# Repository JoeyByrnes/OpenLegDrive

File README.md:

# OpenLeg Drive
Motor Controller for OpenLeg Actuators

This hardware is based on the <a href="https://github.com/mjbots">Moteus r4.5</a> by Josh Pieper at mjbots, and the firmware is ported from Ben Kat's <a href="https://github.com/bgkatz/motorcontrol">motorcontrol</a> project. See the <a href="https://github.com/JoeyByrnes/motorcontrolG4">motorcontrolG4</a> repo for the firmware.

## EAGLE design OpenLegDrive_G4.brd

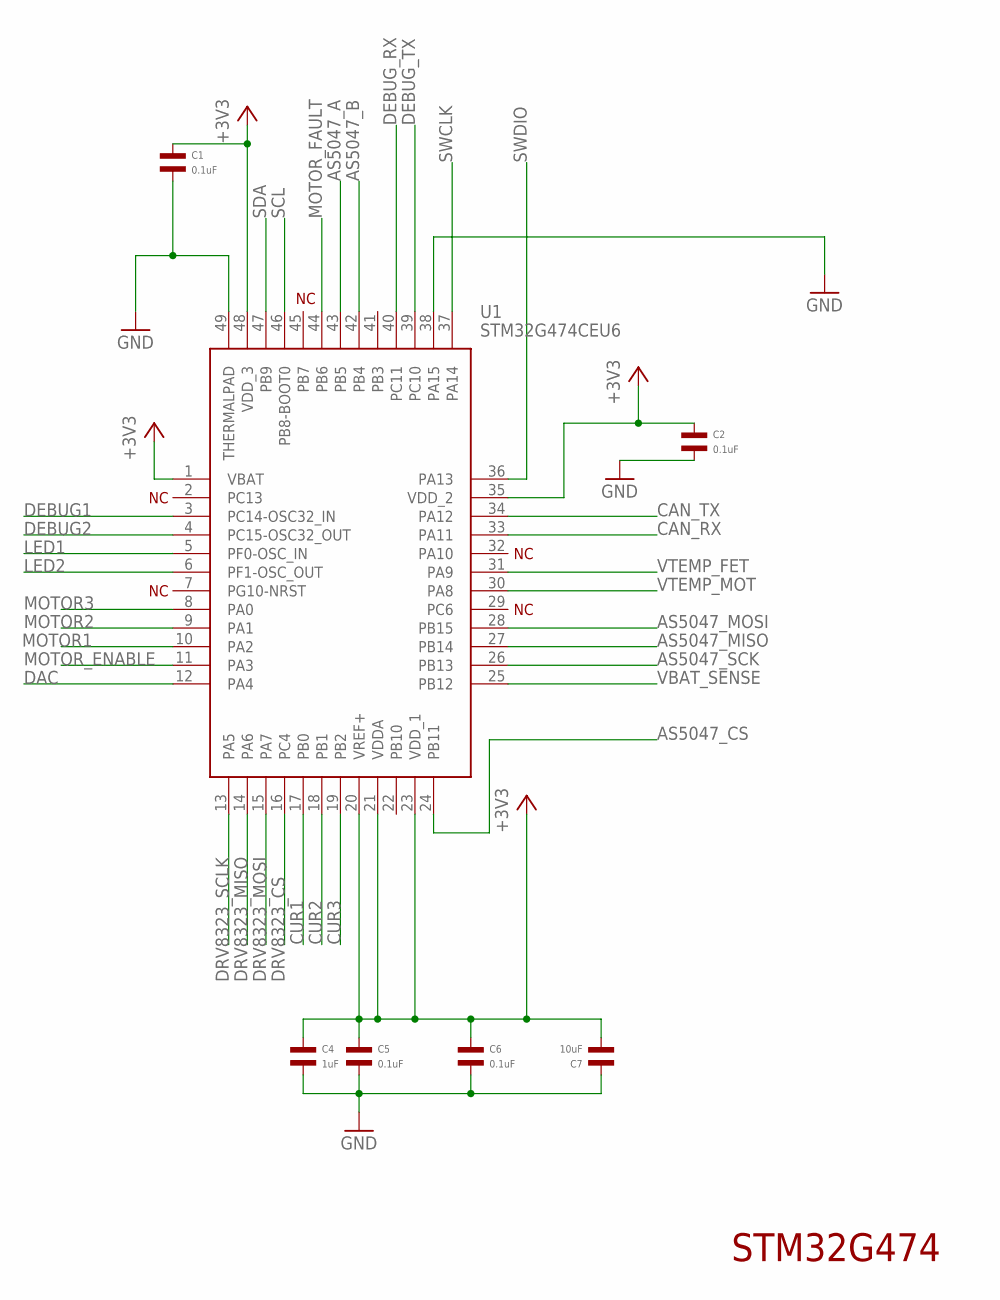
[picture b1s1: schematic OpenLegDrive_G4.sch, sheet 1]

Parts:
C1, C2, C5, C6: 0.1uF; C0402; MPN MF-CAP-0402-0.1uF
C4: 1uF; C0402; MPN MF-CAP-0402-1uF
C7: 10uF; C1206; MPN MF-CAP-1206-10uF
U1: STM32G474CEU6; QFN50P700X700X60-49N; MPN STM32G474CEU6

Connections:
3V3: C1.P$1, C2.P$1, C4.P$1, C5.P$1, C6.P$1, C7.P$2, U1.1 (VBAT), U1.20 (VREF+), U1.21 (VDDA), U1.23 (VDD_1), U1.35 (VDD_2), U1.48 (VDD_3); also elsewhere on the board
AS5047_A: U1.43 (PB5); also elsewhere on the board
AS5047_B: U1.42 (PB4); also elsewhere on the board
AS5047_CS: U1.24 (PB11); also elsewhere on the board
AS5047_MISO: U1.27 (PB14); also elsewhere on the board
AS5047_MOSI: U1.28 (PB15); also elsewhere on the board
AS5047_SCK: U1.26 (PB13); also elsewhere on the board
CAN_RX: U1.33 (PA11); also elsewhere on the board
CAN_TX: U1.34 (PA12); also elsewhere on the board
CUR1: U1.17 (PB0); also elsewhere on the board
CUR2: U1.18 (PB1); also elsewhere on the board
CUR3: U1.19 (PB2); also elsewhere on the board
DAC: U1.12 (PA4)
DEBUG1: U1.3 (PC14-OSC32_IN); also elsewhere on the board
DEBUG2: U1.4 (PC15-OSC32_OUT); also elsewhere on the board
DEBUG_RX: U1.40 (PC11); also elsewhere on the board
DEBUG_TX: U1.39 (PC10); also elsewhere on the board
DRV8323_CS: U1.16 (PC4); also elsewhere on the board
DRV8323_MISO: U1.14 (PA6); also elsewhere on the board
DRV8323_MOSI: U1.15 (PA7); also elsewhere on the board
DRV8323_SCLK: U1.13 (PA5); also elsewhere on the board
GND: C1.P$2, C2.P$2, C4.P$2, C5.P$2, C6.P$2, C7.P$1, U1.38 (PA15), U1.49 (THERMALPAD); also elsewhere on the board
LED1: U1.5 (PF0-OSC_IN); also elsewhere on the board
LED2: U1.6 (PF1-OSC_OUT); also elsewhere on the board
MOTOR1: U1.10 (PA2); also elsewhere on the board
MOTOR2: U1.9 (PA1); also elsewhere on the board
MOTOR3: U1.8 (PA0); also elsewhere on the board
MOTOR_ENABLE: U1.11 (PA3); also elsewhere on the board
MOTOR_FAULT: U1.44 (PB6); also elsewhere on the board
SCL: U1.46 (PB8-BOOT0); also elsewhere on the board
SDA: U1.47 (PB9); also elsewhere on the board
SWCLK: U1.37 (PA14); also elsewhere on the board
SWDIO: U1.36 (PA13); also elsewhere on the board
VBAT_SENSE: U1.25 (PB12); also elsewhere on the board
VTEMP_FET: U1.31 (PA9); also elsewhere on the board
VTEMP_MOT: U1.30 (PA8); also elsewhere on the board

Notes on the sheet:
STM32G474

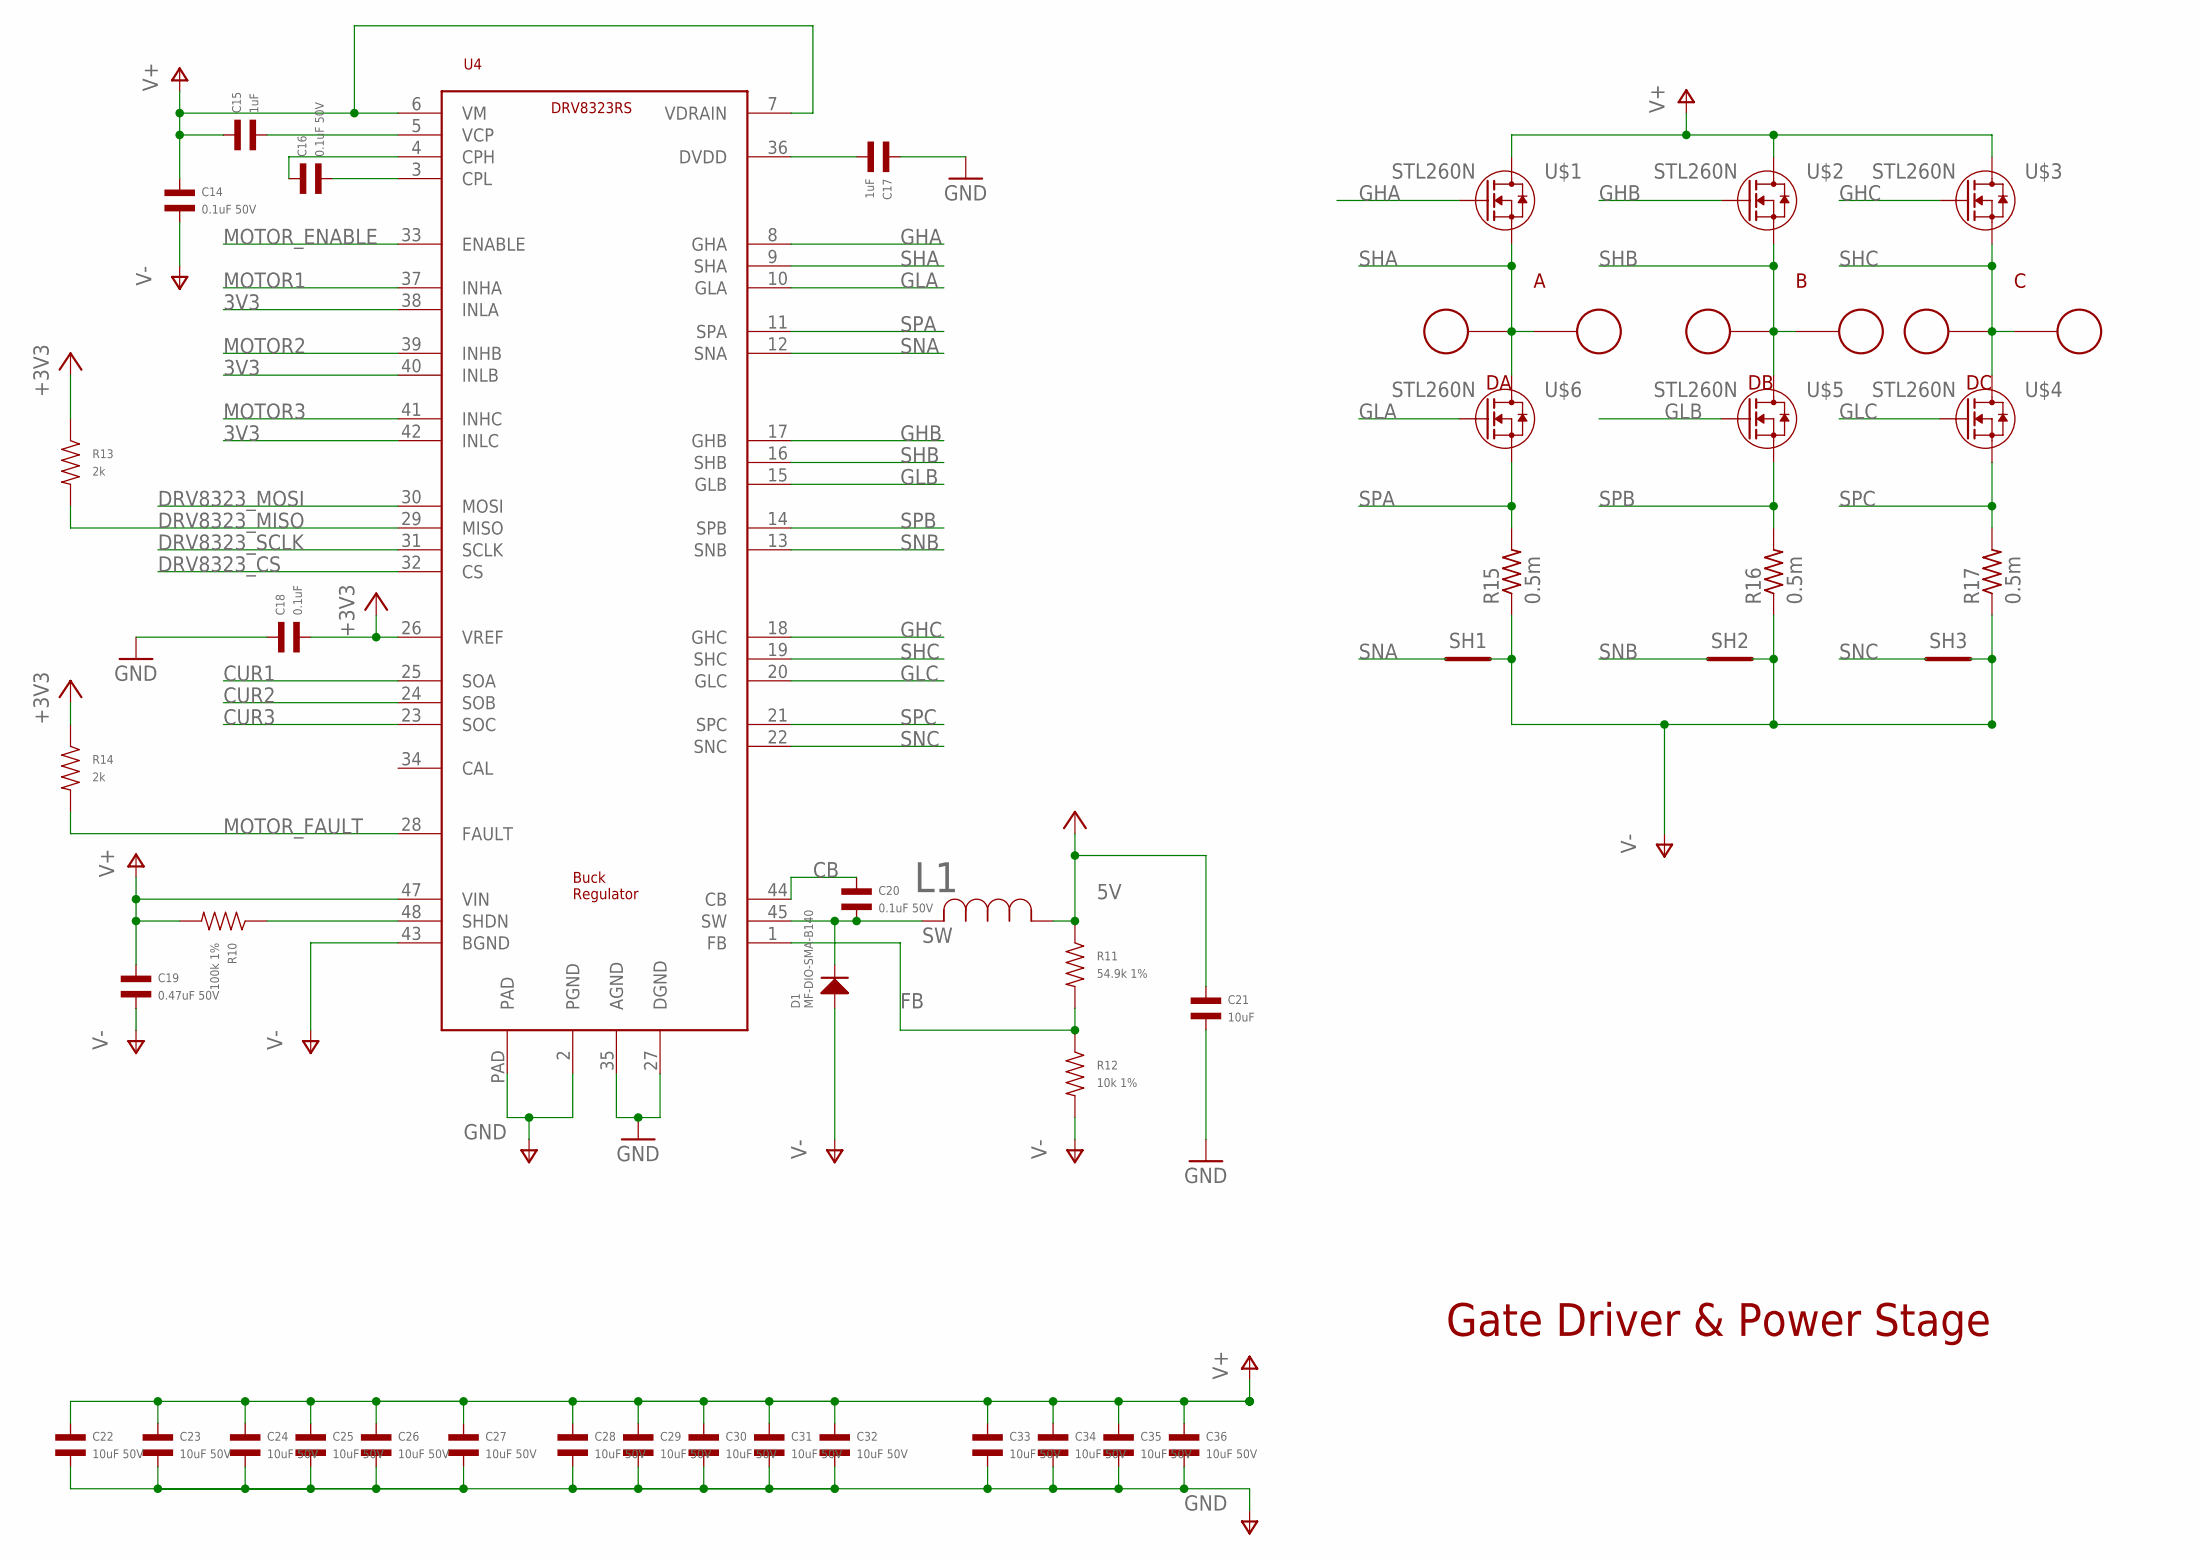
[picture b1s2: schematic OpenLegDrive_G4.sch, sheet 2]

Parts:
A: PAD16AWG_PAD; 16AWG_PAD
B: PAD16AWG_PAD; 16AWG_PAD
C: PAD16AWG_PAD; 16AWG_PAD
C14, C16, C20: 0.1uF 50V; C0402; MPN CGA2B3X7R1H104K050BB
C15, C17: 1uF; C0402; MPN MF-CAP-0402-1uF
C18: 0.1uF; C0402; MPN MF-CAP-0402-0.1uF
C19: 0.47uF 50V; C0402; MPN UMK105ABJ474KV-F
C21: 10uF; C1206; MPN MF-CAP-1206-10uF
C22, C23, C24, C25, C26, C27, C28, C29, C30, C31, C32, C33, C34, C35, C36: 10uF 50V; C1206; MPN C3216X7R1H106K160AE
D1: MF-DIO-SMA-B140; SMA
DA: PAD24AWG_PAD; 24AWG_PAD
DB: PAD24AWG_PAD; 24AWG_PAD
DC: PAD24AWG_PAD; 24AWG_PAD
L1: SRN4018-220M; IND_BOURNS_SRN4018; MPN SRN4018-220M
R10: 100k 1%; R0402; MPN ERJ-2RKF1003X
R11: 54.9k 1%; R0402; MPN ERJ-2RKF3302X
R12: 10k 1%; R0402; MPN ERJ-2RKF1002X
R13, R14: 2k; R0402; MPN MF-RES-0402-2K
R15, R16, R17: 0.5m; R1210
SH1, SH2, SH3: SHORTT5; SHORT_TOP-50
U4: DRV8323RS; PVQFN-N48; MPN DRV8323RSRGZR
U$1, U$2, U$3, U$4, U$5, U$6: STL260N; POWERFLAT_5X6

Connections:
3V3: C18.P$2, R13.P$1, R14.P$1, U4.26 (VREF), U4.38 (INLA), U4.40 (INLB), U4.42 (INLC); also elsewhere on the board
5V: C21.P$1, L1.1, R11.P$1; also elsewhere on the board
CB: C20.P$1, U4.44 (CB)
CUR1: U4.25 (SOA); also elsewhere on the board
CUR2: U4.24 (SOB); also elsewhere on the board
CUR3: U4.23 (SOC); also elsewhere on the board
DRV8323_CS: U4.32 (CS); also elsewhere on the board
DRV8323_MISO: R13.P$2, U4.29 (MISO); also elsewhere on the board
DRV8323_MOSI: U4.30 (MOSI); also elsewhere on the board
DRV8323_SCLK: U4.31 (SCLK); also elsewhere on the board
FB: R11.P$2, R12.P$1, U4.1 (FB)
GHA: U4.8 (GHA), U$1.4 (G)
GHB: U4.17 (GHB), U$2.4 (G)
GHC: U4.18 (GHC), U$3.4 (G)
GLA: U4.10 (GLA), U$6.4 (G)
GLB: U4.15 (GLB), U$5.4 (G)
GLC: U4.20 (GLC), U$4.4 (G)
GND: C14.P$2, C17.P$1, C18.P$1, C19.P$2, C21.P$2, C22.P$2, C23.P$2, C24.P$2, C25.P$2, C26.P$2, C27.P$2, C28.P$2, C29.P$2, C30.P$2, C31.P$2, C32.P$2, C33.P$2, C34.P$2, C35.P$2, C36.P$2, D1.ANODE, R12.P$2, R15.1, R16.1, R17.1, SH1.2, SH2.2, SH3.2, U4.2 (PGND), U4.27 (DGND), U4.35 (AGND), U4.43 (BGND), U4.PAD; also elsewhere on the board
MOTOR1: U4.37 (INHA); also elsewhere on the board
MOTOR2: U4.39 (INHB); also elsewhere on the board
MOTOR3: U4.41 (INHC); also elsewhere on the board
MOTOR_ENABLE: U4.33 (ENABLE); also elsewhere on the board
MOTOR_FAULT: R14.P$2, U4.28 (FAULT); also elsewhere on the board
unnamed: R10.P$1, U4.48 (SHDN)
unnamed: C16.P$2, U4.3 (CPL)
unnamed: C16.P$1, U4.4 (CPH)
unnamed: C15.P$2, U4.5 (VCP)
unnamed: C17.P$2, U4.36 (DVDD)
SHA: A.1, DA.P$1, U4.9 (SHA), U$1.1 (S), U$1.2 (S), U$1.3 (S), U$6.5 (D), U$6.6 (D), U$6.7 (D), U$6.8 (D)
SHB: B.1, DB.P$1, U4.16 (SHB), U$2.1 (S), U$2.2 (S), U$2.3 (S), U$5.5 (D), U$5.6 (D), U$5.7 (D), U$5.8 (D)
SHC: C.1, DC.P$1, U4.19 (SHC), U$3.1 (S), U$3.2 (S), U$3.3 (S), U$4.5 (D), U$4.6 (D), U$4.7 (D), U$4.8 (D)
SNA: SH1.1, U4.12 (SNA)
SNB: SH2.1, U4.13 (SNB)
SNC: SH3.1, U4.22 (SNC)
SPA: R15.2, U4.11 (SPA), U$6.1 (S), U$6.2 (S), U$6.3 (S)
SPB: R16.2, U4.14 (SPB), U$5.1 (S), U$5.2 (S), U$5.3 (S)
SPC: R17.2, U4.21 (SPC), U$4.1 (S), U$4.2 (S), U$4.3 (S)
SW: C20.P$2, D1.CATHODE, L1.2, U4.45 (SW)
V+: C14.P$1, C15.P$1, C19.P$1, C22.P$1, C23.P$1, C24.P$1, C25.P$1, C26.P$1, C27.P$1, C28.P$1, C29.P$1, C30.P$1, C31.P$1, C32.P$1, C33.P$1, C34.P$1, C35.P$1, C36.P$1, R10.P$2, U4.6 (VM), U4.7 (VDRAIN), U4.47 (VIN), U$1.5 (D), U$1.6 (D), U$1.7 (D), U$1.8 (D), U$2.5 (D), U$2.6 (D), U$2.7 (D), U$2.8 (D), U$3.5 (D), U$3.6 (D), U$3.7 (D), U$3.8 (D); also elsewhere on the board

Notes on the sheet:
Gate Driver & Power Stage

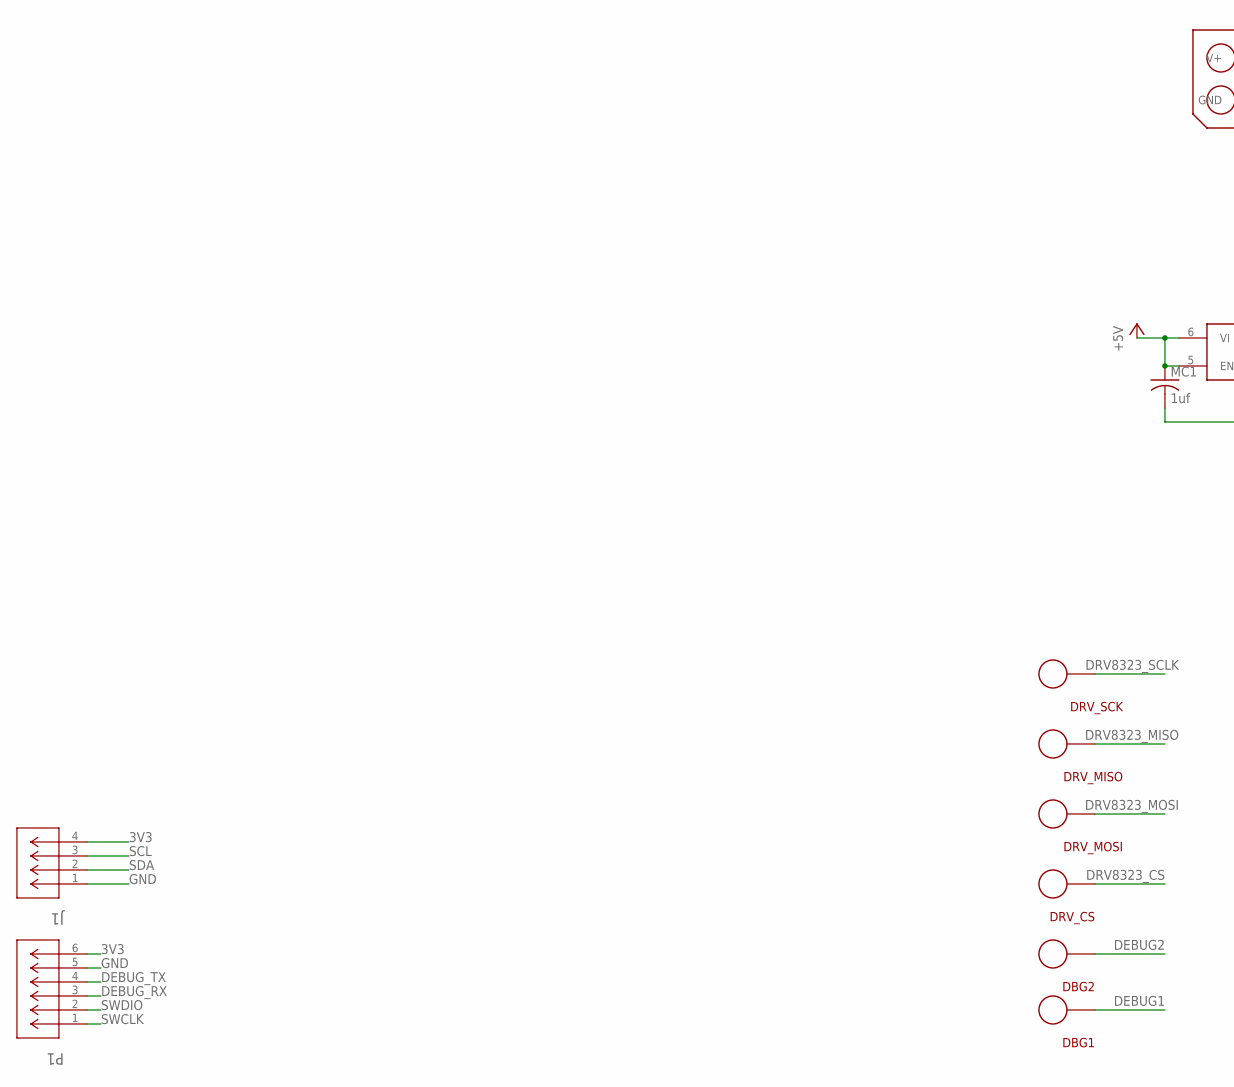
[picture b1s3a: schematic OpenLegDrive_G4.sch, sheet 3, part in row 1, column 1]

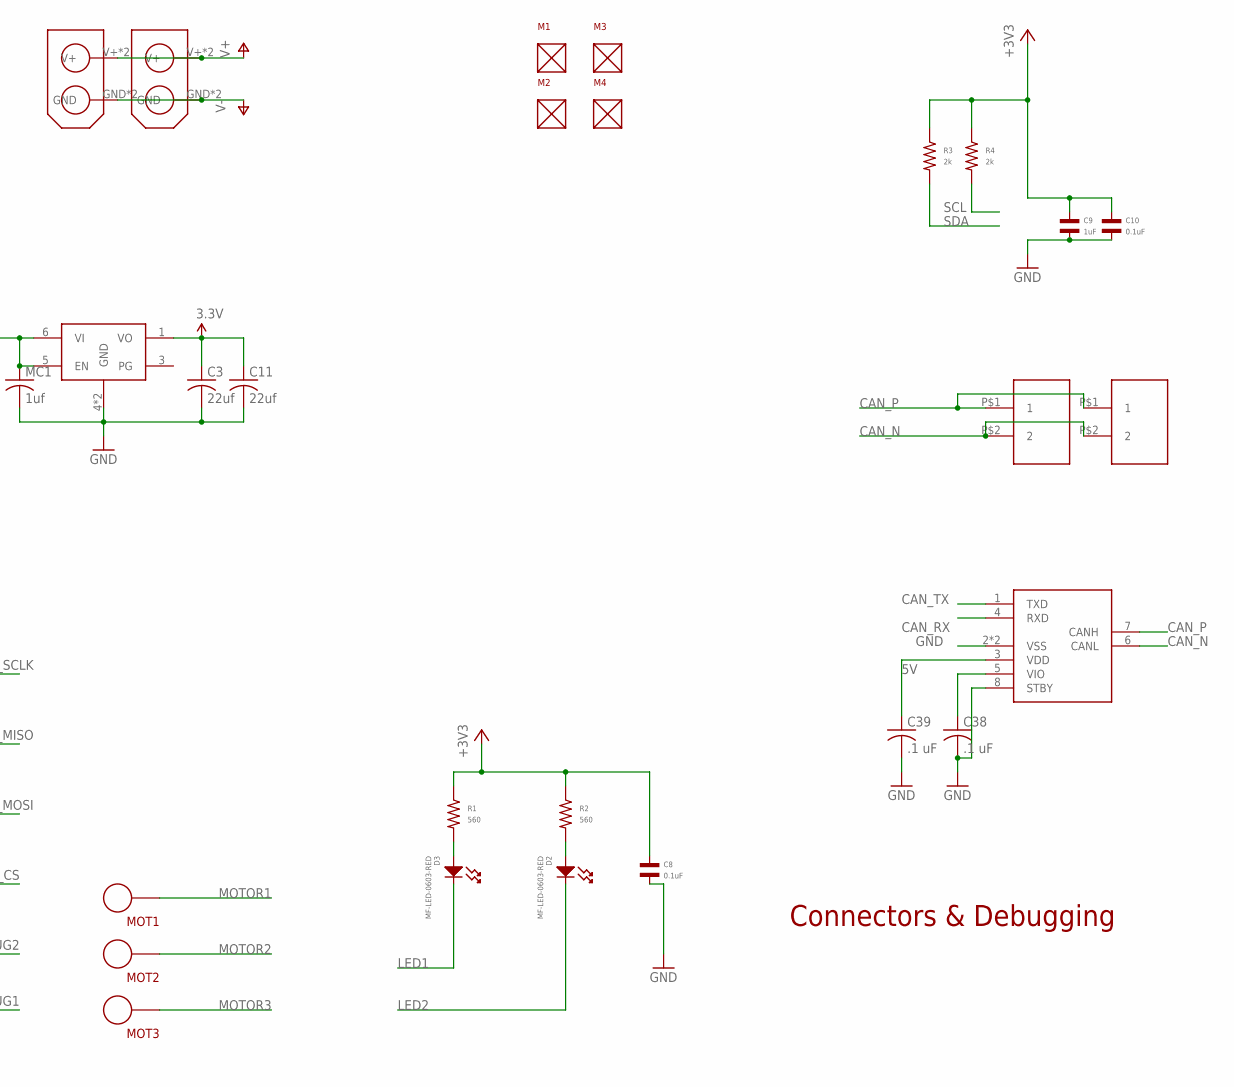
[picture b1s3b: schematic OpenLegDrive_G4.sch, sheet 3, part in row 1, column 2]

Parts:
C3, C11: 22uf; C0603K
C8, C10: 0.1uF; C0402; MPN MF-CAP-0402-0.1uF
C9: 1uF; C0402; MPN MF-CAP-0402-1uF
C38, C39: .1 uF; C0402K
D2: MF-LED-0603-RED; LED0603; MPN MF-LED-0603-GREEN
D3: MF-LED-0603-RED; LED0603
DBG1, DBG2: PAD24AWG_PAD; 24AWG_PAD
DRV_CS: PAD24AWG_PAD; 24AWG_PAD
DRV_MISO: PAD24AWG_PAD; 24AWG_PAD
DRV_MOSI: PAD24AWG_PAD; 24AWG_PAD
DRV_SCK: PAD24AWG_PAD; 24AWG_PAD
J1: S4B-ZR(LF)(SN); CONN_S4B-ZR(LF)(SN)_JST
M1, M2, M3, M4: MOUNT; M2.5MOUNT
MC1: 1uf; C0402
MOT1, MOT2, MOT3: PAD24AWG_PAD; 24AWG_PAD
P1: S6B-ZR(LF)(SN); S6B-ZR_JST
R1, R2: 560; R0402; MPN MF-RES-0402-560
R3, R4: 2k; R0402; MPN MF-RES-0402-2K
U$7: XT30_DUAL_MOUNT_FLIPPED; XT30_DUAL_FLIPPED
U$8: XT30_DUAL_MOUNT; XT30_DUAL
U$9, U$10: JST-PH-DOUBLE-2-PIN; JST-PH_DUALMOUNT-2
U$11: LDFM; DFN6-3X3
U$12: MCP2542; TDFN

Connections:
3V3: C3.1, C8.P$1, C9.P$1, C10.P$1, C11.1, C38.1, J1.4, P1.6, R1.P$1, R2.P$1, R3.P$1, R4.P$1, U$11.1 (VO), U$12.5 (VIO); also elsewhere on the board
5V: C39.1, MC1.1, U$11.5 (EN), U$11.6 (VI), U$12.3 (VDD); also elsewhere on the board
CAN_N: U$9.P$2 (2), U$10.P$2 (2), U$12.6 (CANL)
CAN_P: U$9.P$1 (1), U$10.P$1 (1), U$12.7 (CANH)
CAN_RX: U$12.4 (RXD); also elsewhere on the board
CAN_TX: U$12.1 (TXD); also elsewhere on the board
DEBUG1: DBG1.P$1; also elsewhere on the board
DEBUG2: DBG2.P$1; also elsewhere on the board
DEBUG_RX: P1.3; also elsewhere on the board
DEBUG_TX: P1.4; also elsewhere on the board
DRV8323_CS: DRV_CS.P$1; also elsewhere on the board
DRV8323_MISO: DRV_MISO.P$1; also elsewhere on the board
DRV8323_MOSI: DRV_MOSI.P$1; also elsewhere on the board
DRV8323_SCLK: DRV_SCK.P$1; also elsewhere on the board
GND: C3.2, C8.P$2, C9.P$2, C10.P$2, C11.2, C38.2, C39.2, J1.1, MC1.2, P1.5, U$7.GND, U$7.GND@1 (GND), U$8.GND, U$8.GND@1 (GND), U$11.4 (GND), U$11.EXP (GND), U$12.2 (VSS), U$12.8 (STBY), U$12.9 (VSS); also elsewhere on the board
LED1: D3.CATHODE; also elsewhere on the board
LED2: D2.CATHODE; also elsewhere on the board
MOTOR1: MOT1.P$1; also elsewhere on the board
MOTOR2: MOT2.P$1; also elsewhere on the board
MOTOR3: MOT3.P$1; also elsewhere on the board
unnamed: D3.ANODE, R1.P$2
unnamed: D2.ANODE, R2.P$2
SCL: J1.3, R4.P$2; also elsewhere on the board
SDA: J1.2, R3.P$2; also elsewhere on the board
SWCLK: P1.1; also elsewhere on the board
SWDIO: P1.2; also elsewhere on the board
V+: U$7.V+, U$7.V+@1 (V+), U$8.V+, U$8.V+@1 (V+); also elsewhere on the board

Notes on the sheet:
Connectors & Debugging

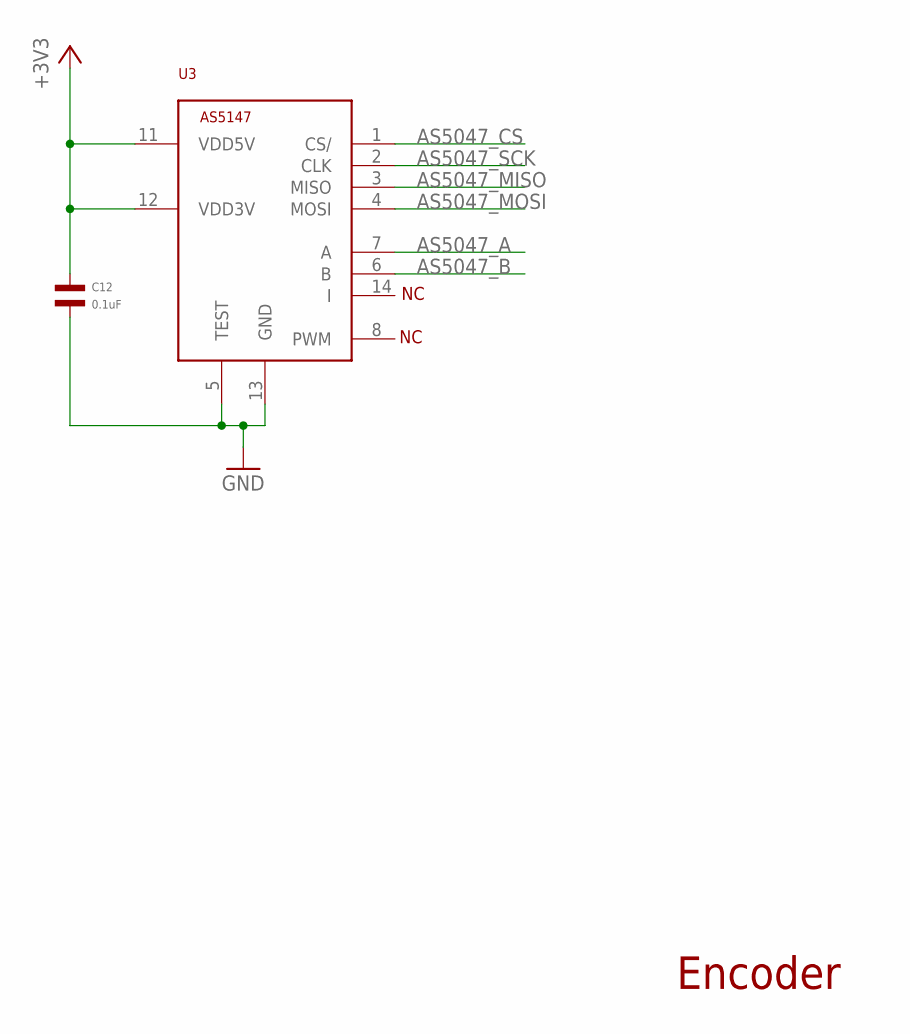
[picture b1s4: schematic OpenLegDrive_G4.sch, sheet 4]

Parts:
C12: 0.1uF; C0402; MPN MF-CAP-0402-0.1uF
U3: AS5147; TSSOP14; MPN AS5047P-ATSM

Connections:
3V3: C12.P$1, U3.11 (VDD5V), U3.12 (VDD3V); also elsewhere on the board
AS5047_A: U3.7 (A); also elsewhere on the board
AS5047_B: U3.6 (B); also elsewhere on the board
AS5047_CS: U3.1 (CS/); also elsewhere on the board
AS5047_MISO: U3.3 (MISO); also elsewhere on the board
AS5047_MOSI: U3.4 (MOSI); also elsewhere on the board
AS5047_SCK: U3.2 (CLK); also elsewhere on the board
GND: C12.P$2, U3.5 (TEST), U3.13 (GND); also elsewhere on the board

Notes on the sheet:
Encoder

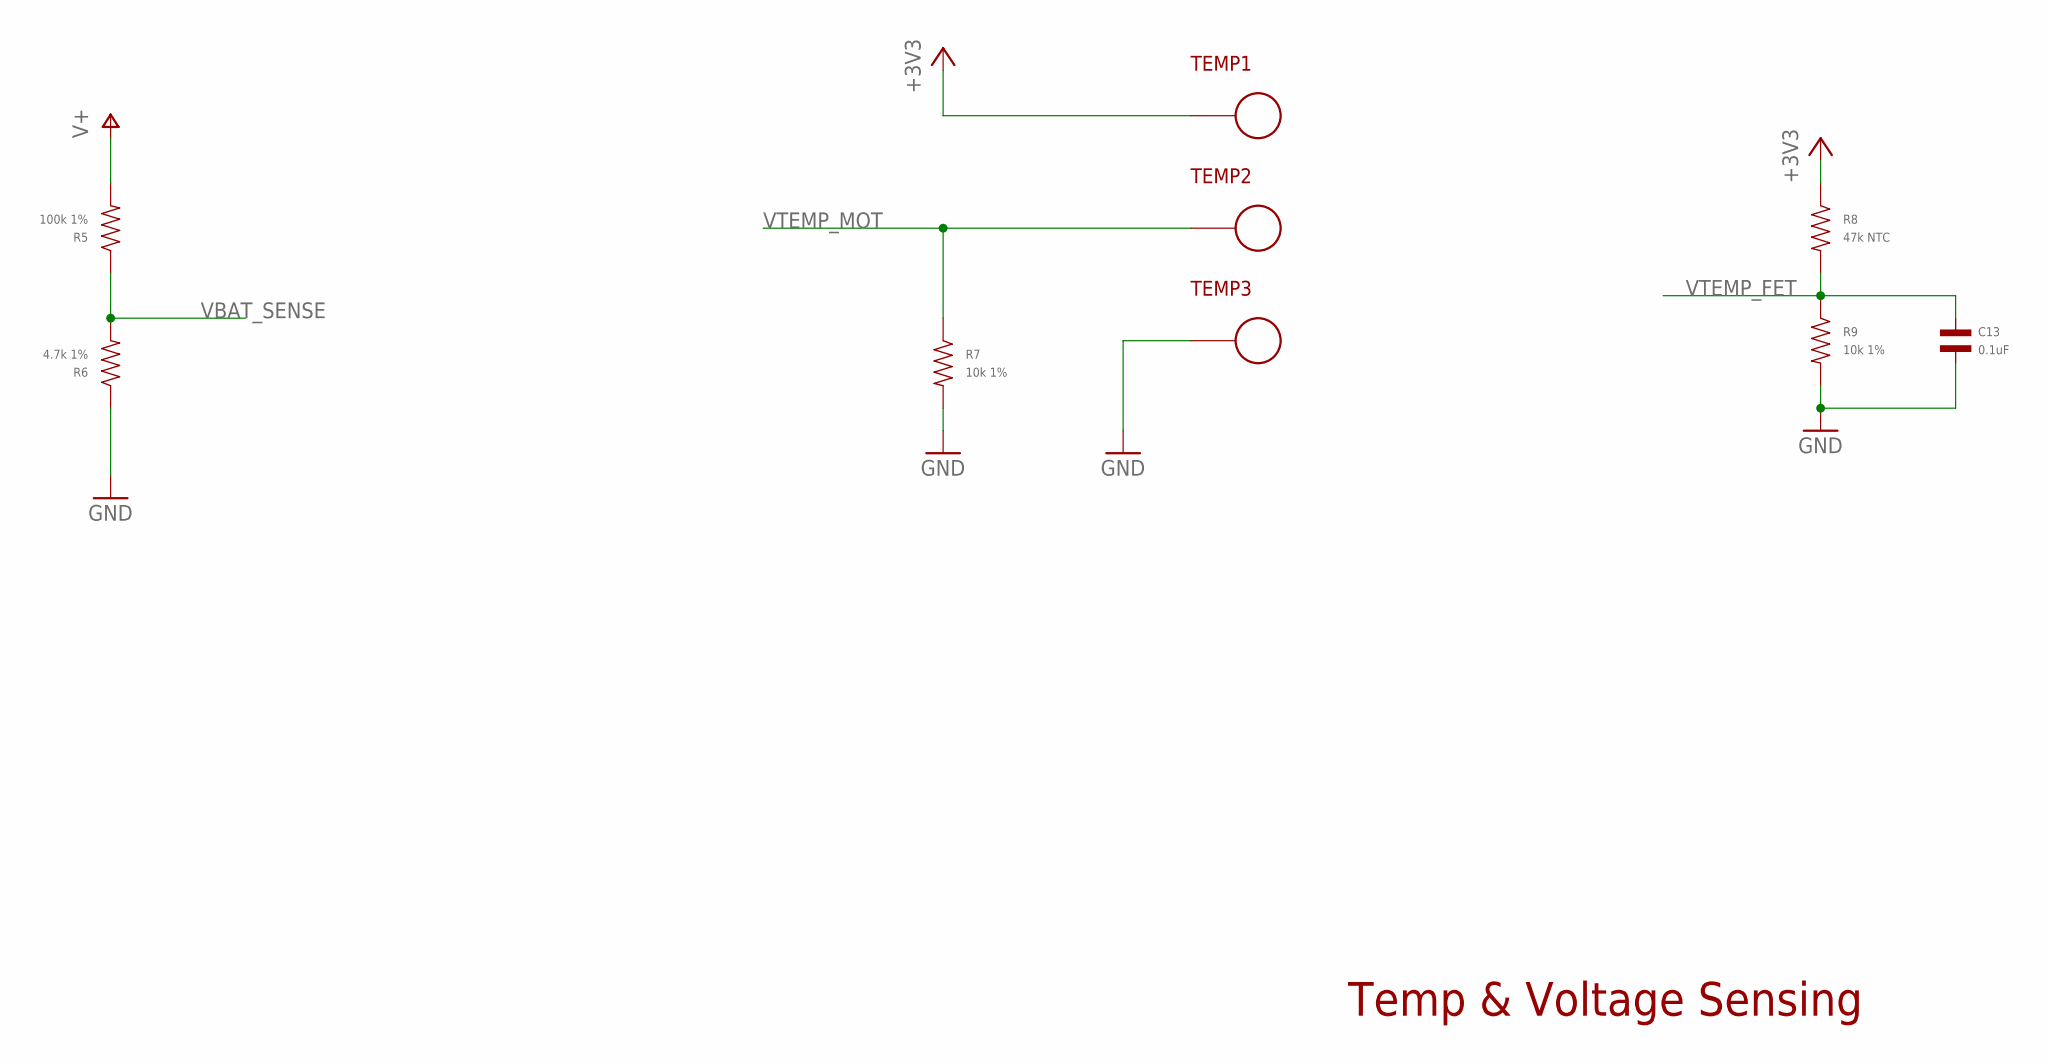
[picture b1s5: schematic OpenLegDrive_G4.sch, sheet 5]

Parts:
C13: 0.1uF; C0402; MPN MF-CAP-0402-0.1uF
R5: 100k 1%; R0402; MPN ERJ-2RKF1003X
R6: 4.7k 1%; R0402; MPN ERJ-2RKF4701X
R7, R9: 10k 1%; R0402; MPN ERJ-2RKF1002X
R8: 47k NTC; R0402; MPN NCP15WB473F03RC
TEMP1, TEMP2, TEMP3: PAD24AWG_PAD; 24AWG_PAD

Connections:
3V3: R8.P$1, TEMP1.P$1; also elsewhere on the board
GND: C13.P$2, R6.P$1, R7.P$2, R9.P$2, TEMP3.P$1; also elsewhere on the board
V+: R5.P$2; also elsewhere on the board
VBAT_SENSE: R5.P$1, R6.P$2; also elsewhere on the board
VTEMP_FET: C13.P$1, R8.P$2, R9.P$1; also elsewhere on the board
VTEMP_MOT: R7.P$1, TEMP2.P$1; also elsewhere on the board

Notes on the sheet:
Temp & Voltage Sensing

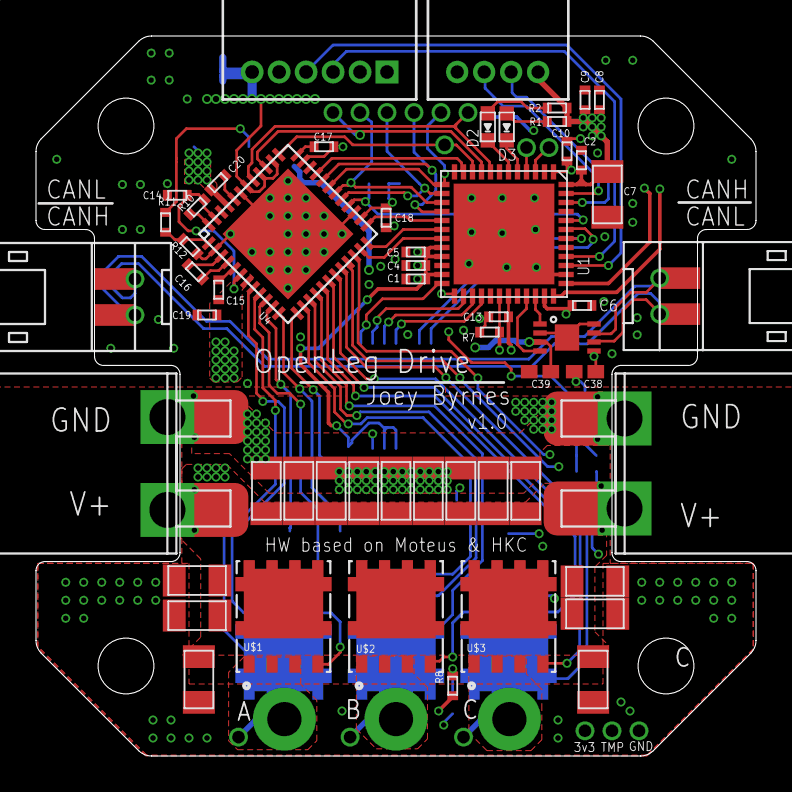
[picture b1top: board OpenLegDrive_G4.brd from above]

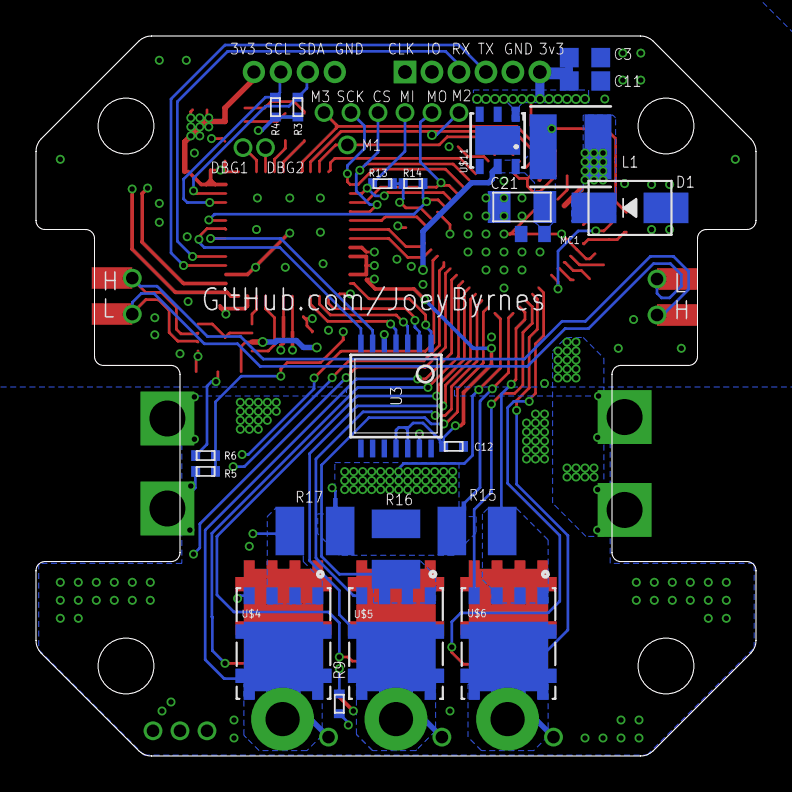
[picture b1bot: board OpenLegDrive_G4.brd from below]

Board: 4 copper layers, 40.0 x 40.0 mm, 102 parts (25 on the bottom side), 64 nets.

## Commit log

2023-10-04 added LICENSE
2023-10-04 added design files

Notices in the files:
OpenLegDrive_G4.sch:
HKC Integrated By Ben Katz (MIT Licence)
Licensed under the Apache 2.0 License
parts and their libraries:
COPYRIGHT: Copyright (C) 2018 Accelerated Designs. All rights reserved
SparkFun-Aesthetics: Licensing: Creative Commons ShareAlike 4.0 International - https://creativecommons.org/licenses/by-sa/4.0
